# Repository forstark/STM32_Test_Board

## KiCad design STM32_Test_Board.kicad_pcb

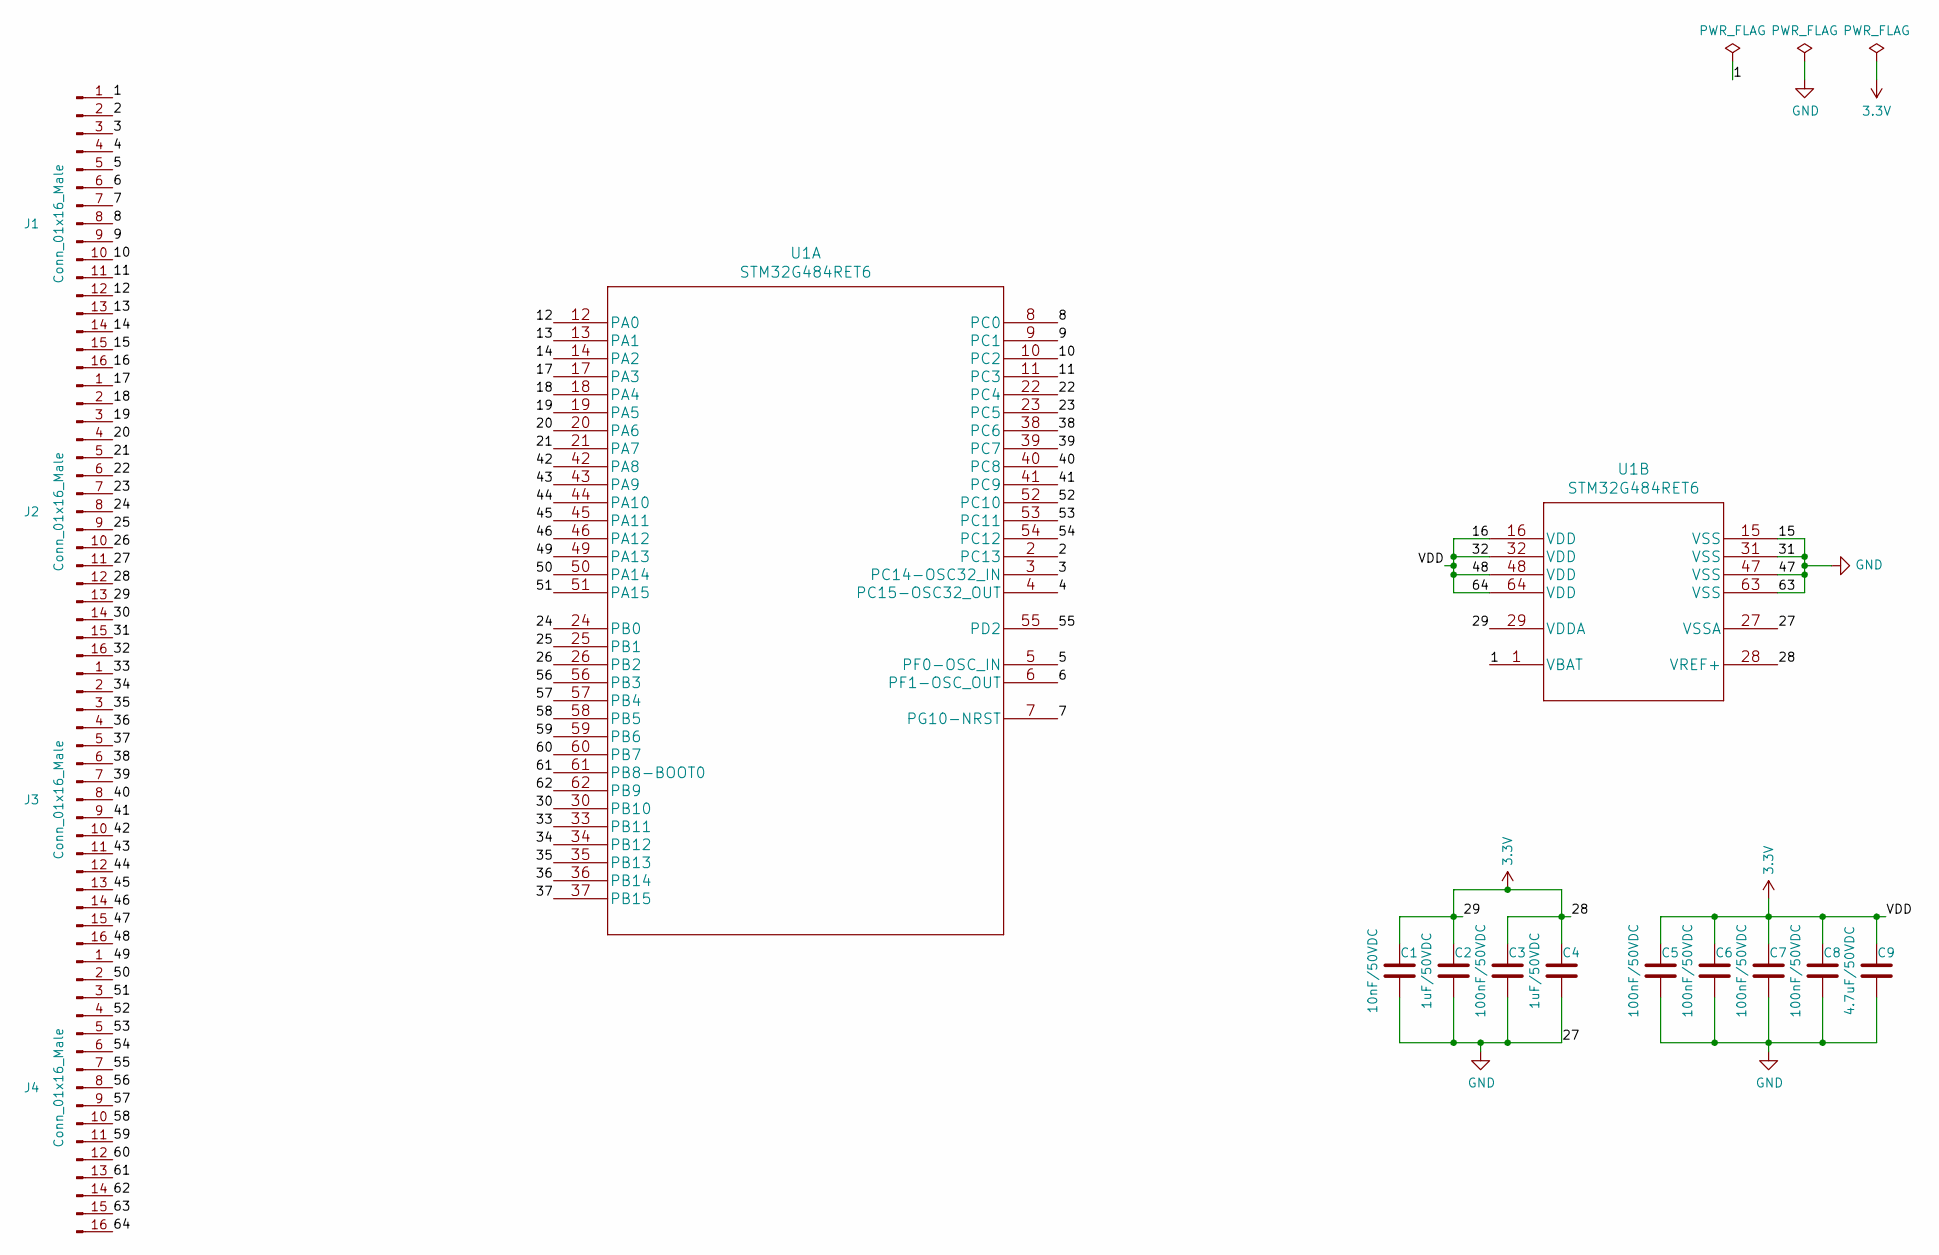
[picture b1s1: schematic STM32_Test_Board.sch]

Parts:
C1: 10nF/50VDC; C_0805_2012Metric_Pad1.15x1.40mm_HandSolder
C2, C4: 1uF/50VDC; C_0805_2012Metric_Pad1.15x1.40mm_HandSolder
C3, C5, C6, C7, C8: 100nF/50VDC; C_0805_2012Metric_Pad1.15x1.40mm_HandSolder
C9: 4.7uF/50VDC; C_0805_2012Metric_Pad1.15x1.40mm_HandSolder
J1, J2, J3, J4: Conn_01x16_Male; PinHeader_1x16_P2.54mm_Vertical
U1: STM32G484RET6; LQFP-64_10x10mm_P0.5mm

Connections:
3.3V: C1.1, C2.1, C3.1, C4.1, C5.1, C6.1, C7.1, C8.1, C9.1, J1.16, J2.12, J2.13, J2.16, J3.16, J4.16, U1.16 (VDD), U1.28 (VREF+), U1.29 (VDDA), U1.32 (VDD), U1.48 (VDD), U1.64 (VDD)
/1: J1.1, U1.1 (VBAT)
/2: J1.2, U1.2 (PC13)
/3: J1.3, U1.3 (PC14-OSC32_IN)
/4: J1.4, U1.4 (PC15-OSC32_OUT)
/5: J1.5, U1.5 (PF0-OSC_IN)
/6: J1.6, U1.6 (PF1-OSC_OUT)
/7: J1.7, U1.7 (PG10-NRST)
/8: J1.8, U1.8 (PC0)
/9: J1.9, U1.9 (PC1)
/10: J1.10, U1.10 (PC2)
/11: J1.11, U1.11 (PC3)
/12: J1.12, U1.12 (PA0)
/13: J1.13, U1.13 (PA1)
/14: J1.14, U1.14 (PA2)
/17: J2.1, U1.17 (PA3)
/18: J2.2, U1.18 (PA4)
/19: J2.3, U1.19 (PA5)
/20: J2.4, U1.20 (PA6)
/21: J2.5, U1.21 (PA7)
/22: J2.6, U1.22 (PC4)
/23: J2.7, U1.23 (PC5)
/24: J2.8, U1.24 (PB0)
/25: J2.9, U1.25 (PB1)
/26: J2.10, U1.26 (PB2)
/30: J2.14, U1.30 (PB10)
/33: J3.1, U1.33 (PB11)
/34: J3.2, U1.34 (PB12)
/35: J3.3, U1.35 (PB13)
/36: J3.4, U1.36 (PB14)
/37: J3.5, U1.37 (PB15)
/38: J3.6, U1.38 (PC6)
/39: J3.7, U1.39 (PC7)
/40: J3.8, U1.40 (PC8)
/41: J3.9, U1.41 (PC9)
/42: J3.10, U1.42 (PA8)
/43: J3.11, U1.43 (PA9)
/44: J3.12, U1.44 (PA10)
/45: J3.13, U1.45 (PA11)
/46: J3.14, U1.46 (PA12)
/49: J4.1, U1.49 (PA13)
/50: J4.2, U1.50 (PA14)
/51: J4.3, U1.51 (PA15)
/52: J4.4, U1.52 (PC10)
/53: J4.5, U1.53 (PC11)
/54: J4.6, U1.54 (PC12)
/55: J4.7, U1.55 (PD2)
/56: J4.8, U1.56 (PB3)
/57: J4.9, U1.57 (PB4)
/58: J4.10, U1.58 (PB5)
/59: J4.11, U1.59 (PB6)
/60: J4.12, U1.60 (PB7)
/61: J4.13, U1.61 (PB8-BOOT0)
/62: J4.14, U1.62 (PB9)
GND: C1.2, C2.2, C3.2, C4.2, C5.2, C6.2, C7.2, C8.2, C9.2, J1.15, J2.11, J2.15, J3.15, J4.15, U1.15 (VSS), U1.27 (VSSA), U1.31 (VSS), U1.47 (VSS), U1.63 (VSS)

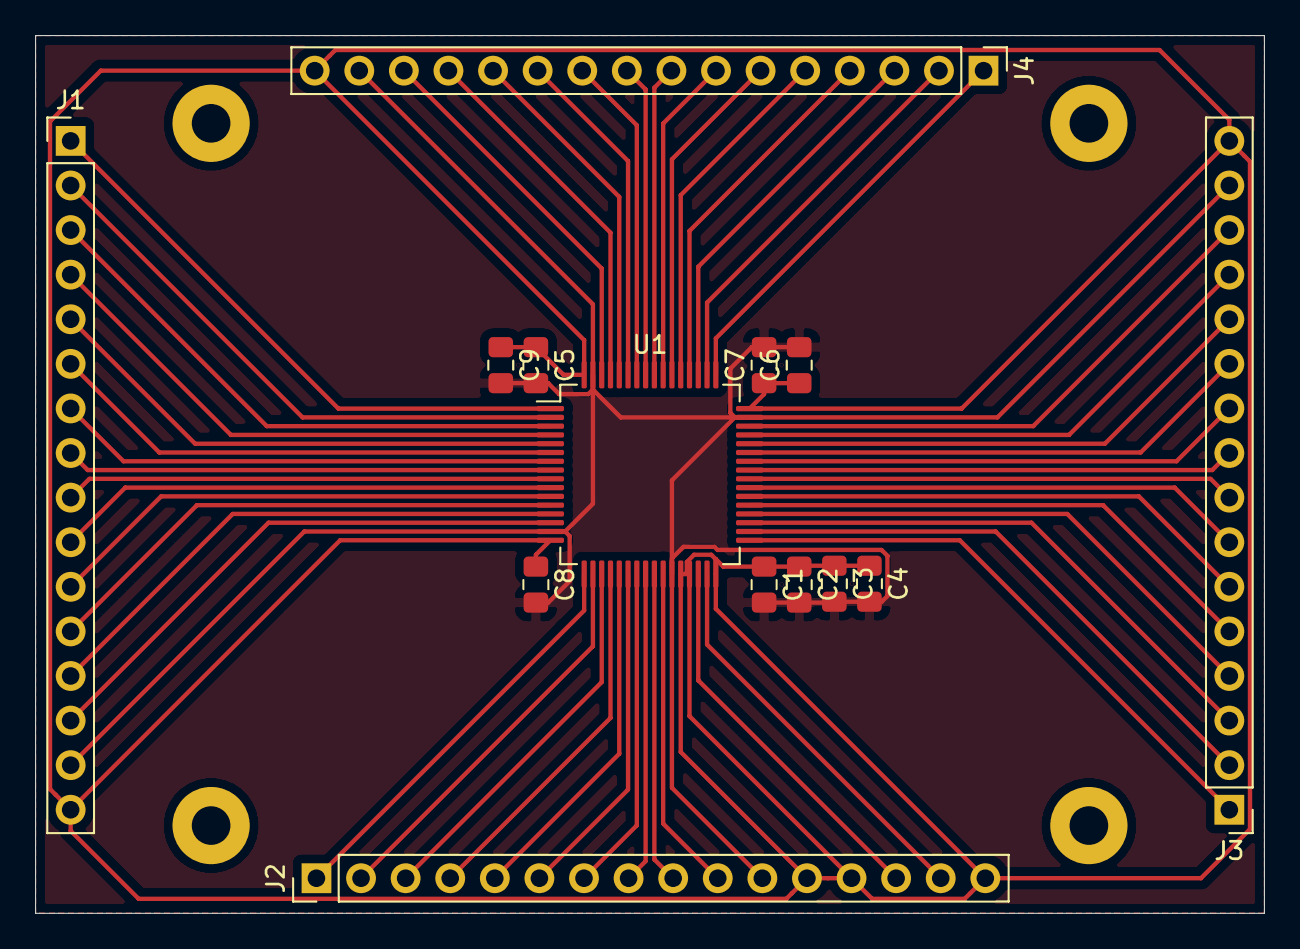
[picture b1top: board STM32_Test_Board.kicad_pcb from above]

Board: 2 copper layers, 70.0 x 50.0 mm, 14 parts (0 on the bottom side), 55 nets.

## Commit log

2021-04-02 Adding PCB design
2021-04-03 Adding decoupling capacitor
2021-04-03 Exporting fabrication files
2021-04-03 Generating files for laser engraving
2021-04-04 Adding readme
2021-04-04 Adding 3D model for housing board
2021-04-05 Updating textures
